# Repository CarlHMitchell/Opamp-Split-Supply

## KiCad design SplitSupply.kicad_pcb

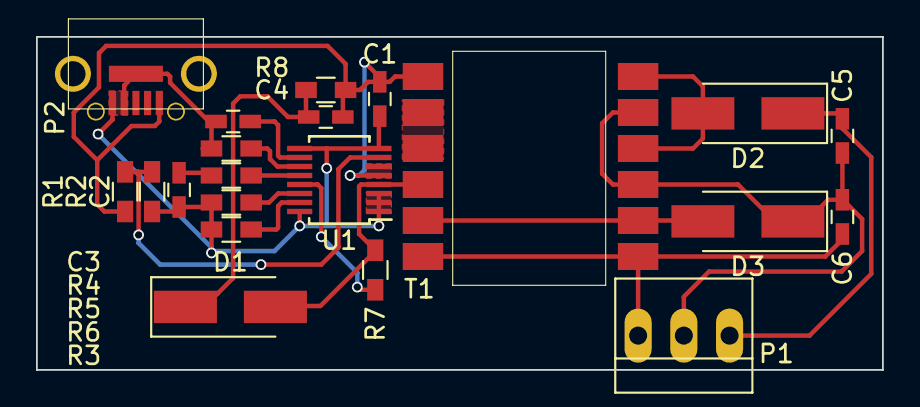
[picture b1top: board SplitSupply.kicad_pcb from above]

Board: 2 copper layers, 47.0 x 18.5 mm, 21 parts (0 on the bottom side), 18 nets.

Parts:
C1: 10u; C_0603_HandSoldering
C2, C3: 10n; C_0603_HandSoldering
C4: 220n; C_0603_HandSoldering
C5, C6: 22u; C_0603_HandSoldering
D1, D2, D3: D140; D_SMA_Handsoldering
P1: CONN_01X03; PINHEAD1-3
P2: USB_B; USB_Micro-B_UJ2-MIBH2-4-SMT_CircMounts
R1: 200k; R_0603_HandSoldering
R2: 90.9k; R_0603_HandSoldering
R3: 80.6k; R_0603_HandSoldering
R4: 10k; R_0603_HandSoldering
R5: 56.2k; R_0603_HandSoldering
R6: 6.04k; R_0603_HandSoldering
R7: 133k; R_0603_HandSoldering
R8: 2k; R_0603_HandSoldering
T1: VersaPAC; VPH1
U1: LT3574; MSOP-16_3x4mm_Pitch0.5mm

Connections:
/GND: C1.2, C2.2, C3.2, P2.4, P2.5, R2.2, R3.2, R4.2, R6.2, U1.1, U1.2, U1.3, U1.8, U1.9, U1.16
/Rref: R6.1, U1.14
/Vcc: C1.1, C4.1, P2.1, R1.1, R8.1, T1.1, U1.5, U1.6
/fb: R7.2, U1.13
/gnd-out: C5.2, C6.1, D3.1, P1.2, T1.9, T1.11
/neg-out: C6.2, P1.3, T1.6, T1.7
/pos-out: C5.1, D2.1, P1.1
/pwr-in: R1.2, R2.1, U1.7
/rlim: R4.1, U1.11
/ss: C3.1, U1.10
/swfb: C4.2, D1.1, R8.2
/switch: D1.2, R7.1, T1.4, U1.4
/tc: R3.1, U1.15
/vc: R5.1, U1.12
/vc2: C2.1, R5.2
unnamed: D2.2, T1.10, T1.12
unnamed: D3.2, T1.5, T1.8
unnamed: T1.2, T1.3

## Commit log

2017-12-22 initial commit for GitHub
2017-12-22 Setup .gitignore
